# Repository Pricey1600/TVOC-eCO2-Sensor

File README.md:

# TVOC & eCO2 Sensor
A DIY TVOC &amp; eCO2 sensor for integration into Home Assistant using ESP-Home.

## Project Outline
A DIY Total Volatile Organic Compounds (TVOC) and equivalent Carbon Dioxide (eCO2) sensor to measure the air quality within my room. This is particularly important due to the recent addition of a 3D printer within the space. I'd also like this sensor to be able to connect to my Home Assistant instance to be able to consolidate and manage it alongside existing smart home sensors.

## Components
- Seeed XIAO ESP32C3 board
- CCS811 HDC1080 eCO2 and TVOC sensor
- Custom PCB
- Blue LED
- 100 ohm resistor
- 3D Printed enclosure

## Prototype
Built using a breadboard. The ESP board communicates with Home Assistant via ESP-Home and controls power input and distribution. The TVOC/eCO2 sensor is wired up to the ESP board and reports the current TVOC and eCO2 values every 15 seconds. The Blue LED acts as a status light and flashes when the device is disconnected from the Home Assistant instance but can also be toggled manually from the Home Assistant dashboard.

## Initial Enclosure Design
Initial enclosure designs focused on keeping the components separate without the use of a custom PCB due to my lack of experience with PCB design. All enclosure designs would be done in Autodesk Fusion 360 as it is one of the most widely used hard surface modelling packages that offers a free version for hobbyists. The first few versions featured a slot for the ESP board to be pressed into and held into place at the corners, a shelf for the CCS811 HDC1080 sensor board itself (to allow routing of cables underneath), and a friction fit mount for the LED. These components would then be covered with a slide-on lid and mounted to the wall using a dovetail wall plate. 

## PCB Design
Eventually I decided that it made a lot more sense to take the time to learn some PCB design in order to keep the sensor compact and improve the overall look. After some research I decided to use KiCad due to the large amount of online tutorials and it being free to use. The PCB design took roughly 2 days to finalise and was sent to PCBWay for manufacture.

## PCB Enclosure Design
After changing to using a PCB to hold all of the components the sensor enclosure had to be altered as well. Luckily, this was not a long process as I only had to worry about holding the PCB in place rather than the individual components and so most of the difference between versions were just slight tolerance changes.

## The Final Design

## Conclusion
During this project I have learned a lot about PCB design and smart home integration using ESP-Home that I can carry over to future projects. However, I do have some regrets with this project:
- Low accuracy components - While the CCS811 HDC1080 sensor does provide some rough idea of air quality it doesn't come pre-calibrated and doesn't provide an accurate CO2 reading. I should have done more research into the types on sensors available and maybe spent a bit more for a higher quality sensor.
- Late switch to PCB - Deciding to use a custom PCB design earlier in the project could have cut the complexity of the enclosure and project length in half.
- No battery power - The Seeed XIAO ESP32C3 has a built in charging circuit that was not taken advantage of during this project.

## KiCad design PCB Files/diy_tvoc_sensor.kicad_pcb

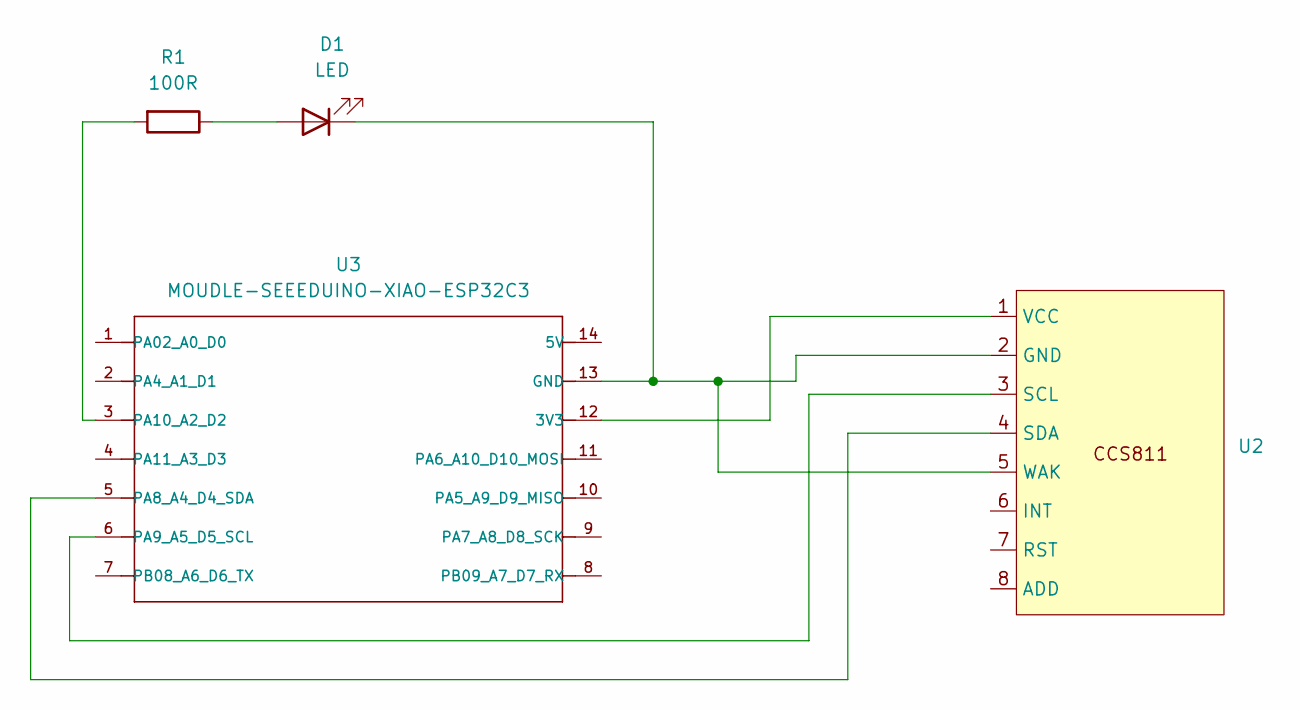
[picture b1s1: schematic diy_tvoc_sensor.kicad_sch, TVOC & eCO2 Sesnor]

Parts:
D1: LED; LED_D5.0mm_Clear
R1: 100R; R_Axial_DIN0207_L6.3mm_D2.5mm_P7.62mm_Horizontal
U2: CCS811_CJMCU-8118
U3: MOUDLE-SEEEDUINO-XIAO-ESP32C3; MOUDLE14P-SMD-2.54-21X17.8MM

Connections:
unnamed: D1.2 (A), R1.1
unnamed: D1.1 (K), U2.2 (GND), U2.5 (WAK), U3.13 (GND)
unnamed: U2.3 (SCL), U3.6 (PA9_A5_D5_SCL)
unnamed: U2.4 (SDA), U3.5 (PA8_A4_D4_SDA)
unnamed: U2.1 (VCC), U3.12 (3V3)
unnamed: R1.2, U3.3 (PA10_A2_D2)

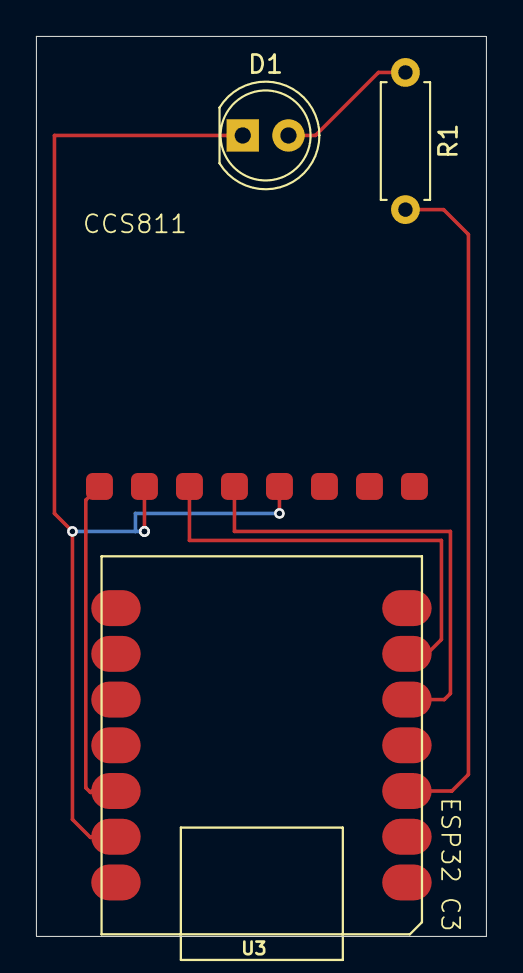
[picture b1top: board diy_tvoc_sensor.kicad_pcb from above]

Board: 2 copper layers, 25.0 x 50.0 mm, 4 parts (0 on the bottom side), 6 nets.

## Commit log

2025-01-19 Uploading Project Files
2025-01-19 Added ESP-Home Yaml File
